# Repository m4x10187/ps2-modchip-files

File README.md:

# PS2 Modchip Archive

This is a repository that aims to archive everything related to modchips for the "PlayStation 2" (PS2) video game console for the foreseeable future.

It is meant to be a continuation to Will's Console Modifications' [PS2 Modchip Wiki](https://www.willsconsolemodifications.co.uk/ps2-wiki/index.php) (not affiliated).

# Frequently Asked Questions (FAQ)

## How can I contribute to the repository?
Do you have any diagram/s or any of the above that fit the criteria? If they do not exist in the repository, then you are more than welcome to create an issue with included files so that it can be added.

# Credits
- DMS3 FPGA source code and Messiah 2 source code, courtesy of [asmblur](https://github.com/asmblur).
- H2o modchip source code and gerber files, courtesy of summ0ne.
- PCB design/soldering assistance and documentation from [AtherisMods](https://github.com/AtherisMods).
- [Crystal Chip R34 V5](https://github.com/saildot4k/Crystal-Chip-R34-v5), a continuation of the Crystal Chip Boot Manager and Firmware by [R3Z3N](https://github.com/saildot4k).
- [Crystal Chip Team](https://ps2modchiptutorials.com/crystal-chips/cc-site-backup/index.htm) for developing an incredibly stable and amazing modchip.
- [Will's Console Modifications](https://www.willsconsolemodifications.co.uk/ps2-wiki/chips.php) for his PS2 modchip showcase wiki.
- Thanks to [PS2 Modchip Tutorials](https://ps2modchiptutorials.com) and [GBAtemp](https://gbatemp.net/) for promoting this repository.

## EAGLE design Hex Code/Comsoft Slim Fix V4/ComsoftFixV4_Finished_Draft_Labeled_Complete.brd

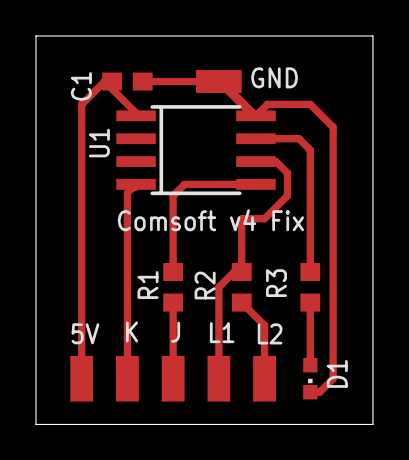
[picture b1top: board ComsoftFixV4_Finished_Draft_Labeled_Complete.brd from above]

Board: 2 copper layers, 18.7 x 21.6 mm, 12 parts (0 on the bottom side), 9 nets.

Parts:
5V: 5V; SMD1,27-2,54
BLUED1: 24mA; CHIPLED_0603
C1: 0.1uF; C0603
GND: GND; SMD1,27-2,54
J: J; SMD1,27-2,54
K: K; SMD1,27-2,54
L1: L1; SMD1,27-2,54
L2: L2; SMD1,27-2,54
R1: 1.5K; R0603
R2: 10K; R0603
R3: 100; R0603
U1: PIC12C508SM; SO-08M

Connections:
GND: BLUED1.C, C1.1, GND.1, U1.8
K: J.1, R1.2
unnamed: BLUED1.A, R3.1
unnamed: L1.1, R2.2, U1.6
unnamed: 5V.1, C1.2, U1.1
unnamed: L2.1, R2.1
unnamed: R1.1, U1.5
unnamed: K.1, U1.4
unnamed: R3.2, U1.7

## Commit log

2023-05-10 Added firmware updates
2023-05-10 Added flash chip dumps
2023-05-10 Uploaded hex files
2023-06-14 Added Mars Pro flash dump
2023-06-15 Modbo 5.0D
2023-06-19 Added chip diagrams.
2023-06-23 Added Infinity PSX DESR and MXL2 diagrams.
2023-06-25 More diagrams.
2023-06-27 Added new diagrams for Matrix PIC fix
2023-07-04 Updated Mars Pro diagrams
2023-07-05 Mars A752, MA-302, GM-603, GM-805SL, Thunder Chip.
2023-07-11 Magic 3.1+ and Magic 3.2.
2023-07-11 Source code for Messiah 2 and Origa Chip.
2023-07-18 Added Aladdin chips.
2023-07-18 Added Magic Mushroom update.
2023-08-14 Added Muppet V12 diagrams.
2023-08-14 Added Muppet diagrams
2023-08-20 Mod8
2023-08-22 DMS, DMS3, Matrix MX4 updates
2023-08-22 DMS4 update
2023-08-22 CrystalChip diode fix
2023-08-22 Myth Chip
2023-08-22 Ice Team laser fix
2024-01-21 Re-organised laser fixes and RGB mods, added new Prodigy chip diagrams.
2024-01-21 Renamed the "H2O" directory to "H2O & H2O+", new Super DMS 3.3 diagrams,
2024-01-21 New CrystalChip files.
2024-01-21 New firmwares: DMS4, G2, O2chip, MX4.
2024-01-27 Added FINAL-fix.RAR
2024-02-04 Added "Saintless"
2024-02-22 Added "Messiah 2" Installation docs
2024-02-26 Added "Ultra", "Marvel V9/V10", "NH7", "NH8".
2024-02-28 Added additional Installation Diagrams
2024-03-02 Added Magic 3.5/3.6 diagrams.
2024-03-08 Added Octapus 3D diagrams
2024-03-09 Added Apple 3, Apple Chip AIO, Mini Apple, AppleES
2024-03-09 Added Apple 2 and Apple Pro
2024-03-13 Added "ZeN"
2024-03-14 Added NH3, NH7, Matrix MX3 (DNS-1003)
2024-03-14 Remove old NH7 directory
2024-03-14 Added V5 Neo Key diagram.
2024-03-14 Added Autokey Instructions
2024-03-15 Added Mini Duo 2, Advance 2.1 and Magic 4
2024-03-20 Magic 4 switch diagram.
2024-03-20 Mars Pro (GM-603) V10 diagram.
2024-03-20 Added Mars Pro (GM-816), (GM-806) and (GM-806HD).
2024-03-24 Added Neo 12
2024-03-24 Added "Diamond" and "Neo Magic"
2024-03-24 Reupload ToxicBIOS files
2024-03-24 Apple II V4 & GH005-010 diagrams
2024-03-25 HD Combo 2 diagrams (V5-V16C)
2024-03-25 HD Combo V4 & V7 diagrams
2024-03-25 Added LI30 072-42 chip.
2024-03-26 Added NH8+ and NEO 4.5
2024-03-27 Added Lisa XP and Lisa II GZero
2024-03-30 Added "Matrix MXL-4 (DNS-1013)"
2024-03-31 Added "Octapus Rev"
2024-04-02 Added "Messiah 750"
2024-04-02 XenoPS V18 and V4 diagrams (same as Modbo)
2024-04-02 Added "TNT" diagrams
2024-04-02 Prodigy 4/4 TE V17 and V16 diagrams.
2024-04-02 Added "HD Chip"
2024-04-05 Magic V - V9 diagram.
2024-04-05 Added "Magic-S+"
2024-04-05 Added "MegaSX2"
2024-04-06 Magic Pro V9 diagram
2024-04-06 Magic Pro V9 diagram (fixed)
2024-04-06 Added "Apple 70K"
2024-04-16 Added "RSM-MOD V9-V10" and "Mimy Chip".
2024-04-18 Modbo dumps by "Atheris"
2024-05-05 Added H2O sources (courtesy of 1nick9)
2024-05-05 Added "Messiah" diagrams (courtesy of 1nick9).
2024-05-06 Added "H2o (B-FLEX)" (thanks 'summ0ne')
2024-06-11 Added "Matrix Infinity ZL (DNS-1016)"
2024-06-20 Added "Messiah 5.0+" and "Messiah 7.5"
2024-12-08 Added "Matrix Infinity SL (DNS-1014)"
2025-01-22 Reorganized and added R34V3
    Reorganized and added R34V3
    To come, R34v3 will include more apps to make it an AIO (all-in-one) and eventually include VMCs for SD2PSX and MemCardPro2
2025-01-26 Added DMS3 FPGA source code
2025-01-27 Added MMCE support
    MMCE support added.
2025-02-04 Updated CC scripts and added new BM Megapack
2025-02-20 Added newest G2 install diagrams, and missing v14-15
2025-03-20 Ice Manager utility for Magic Ice chips.
2025-03-22 Messiah 3.2 chip diagrams
2025-04-14 Added "Matrix (DNS-1001)"
2025-04-15 Added chip pic for "RSM-MOD V9/V10".
2025-04-24 Additional GM-806 diagrams for SCPH-7x series.
2025-04-25 Diagrams and instructions for Improver 3 (MXE-5L)
2025-04-25 F14 chip picture
2025-04-25 V12 diagram for GM-805SE
2025-04-25 New diagrams: Auto-588 (Magic Pro)
2025-04-25 Added laser fix diags: PRO-6508
2025-04-25 V12 diagram for GM-805SL.
2025-04-25 Added new diagrams: Mars II (MA-501)
2025-04-25 Added new diagrams: DMS Kingplayer
2025-04-26 Added diagrams: Super-7 (2005)
2025-04-26 Added new diagrams: M-7 (GP-698 - GP-758)
2025-04-26 Delete Diagrams/M-7 (GP-698)/GP-698_E-72.jpg
    Removed old low-res diagram.
2025-05-06 New diagrams: Nemesis, Nemesis Pro, Excalibur.
2025-06-22 Mars Pro GM-806 (SCPH-5000x - 700xx)
2025-06-26 Added "Ninjamod" diagrams.
2025-06-29 Added 'Apple EX'
2025-07-04 Moved V9 diagram to Magic V50K.
2025-07-05 Crystal Chip v1.1 diagrams
2025-07-05 Dupe
2025-07-05 Added "Mars Chip"
2025-07-07 High quality Magic VKX+ diagram for V12
2025-07-07 ChipMod V7/V8 diagrams.
2025-07-07 New chip diagrams: Titan SX2
2025-07-07 Infinity 2.0 clone firmware - dumped by 1nick9
2025-07-07 Modbo V1.1 with firmware 1.4 - dump by bunghoolio
    https://web.archive.org/web/20090423124051/http://psx-scene.com:80/forums/ps2-modchips/38513-have-you-killed-your-modbo.html
    Notes:
    - Firmware 1.5 does not work on Modbo V1.1/V1.2 due to anti-clone protection.
2025-07-08 Ghost 2 RC3 v2.21
2025-07-09 DMS4 EZI Installation Manual v1.4
2025-07-09 Added new diagrams: DMS4 EZI SE
2025-07-09 Ghost 2 Recovery CD v1.0 & G2 FW v1.31
2025-07-11 Added diagrams: Titan SX
2025-07-11 Ice Manager PS2 application
2025-07-11 Ripper 3 firmware updates
2025-07-12 Added new diagrams: Sumo 207
2025-07-17 New diagrams: Added "Nova Chip"
2025-07-18 Added diagrams: Slim Chip 70K
2025-07-18 Added diagrams: Murano-III Grande
2025-07-20 Slimline Fix diagrams for V14 through V16.
2025-07-20 New diagrams: Neo-Fix V12
2025-08-03 V0/A-B Chassis diagram - permission from BreadFang
2025-08-07 Decompiled source code for PIC Fix v2.0
